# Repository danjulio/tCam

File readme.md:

## ESP32-based Thermal Imaging Cameras
tCam, tCam-Mini, tCam-POE and tCam-Eth are four cameras designed by Dan Julio around the ESP32 and Lepton 3.5.  They provide easy access to radiometric data from the Lepton — per-pixel temperature information that survives into saved files and enables real analysis, not just pretty pictures.

This fork modernizes the **tCam-Mini firmware** into a fully self-contained instrument: the camera serves its own app to any browser, roams between WiFi networks, updates itself over the air, and needs no software installed anywhere.  The original json protocol on port 5001 is untouched, so every existing client — desktop app, Python scripts, mobile apps — keeps working.

### Quick start (this firmware)
1. Flash `tCam-Mini/firmware` (see [BUILDING_WINDOWS.md](tCam-Mini/firmware/BUILDING_WINDOWS.md)) — or upload a built `tCamMini.bin` through the web UI of any camera already running FW 4.0+.
2. Power the camera.  It joins a saved WiFi network, or broadcasts its own `tCam-Mini-XXXX` hotspot.
3. Connect and browse to **http://192.168.58.1/** (hotspot) or **http://tcam-mini.local** (your network).  That's the whole app.

| | |
|---|---|
|  |  |
| *Instrument-dense settings; the ⓘ button reveals help text.* | *Full toolbar and readouts on a phone.* |

More interface detail and screenshots: [WEB_UI.md](tCam-Mini/firmware/WEB_UI.md)

### Find the camera after it moves — tCam Finder

A saved browser shortcut freezes an IP address, but a camera that roams between houses
gets a different one at each location, so the shortcut opens a dead address. **tCam
Finder** fixes that with a page whose own address never changes: it asks the camera —
over Bluetooth LE — where it is *right now*, then opens its interface.

**➡️ [Open tCam Finder](https://mcgeaverbeaver.github.io/tCam/)** — save *this* page to
your home screen instead of the camera's IP.

| | |
|---|---|
|  |  |
| *Find by Bluetooth, plus every camera it has seen before.* | *[▶ Watch the demo](https://youtube.com/shorts/R_bb3d-skMs)* |

Bluetooth is used for **discovery only** — one read of the camera's name, current address
and mode. Video then streams over WiFi at full speed through the normal web interface.
There is no cloud service, no account and no backend: the page is static, all camera
traffic stays on your LAN, and the remembered-camera list lives only in your own browser.
Because the finder's origin is stable, that list survives the address changes that break
a camera-hosted shortcut.

* **Android / Windows / any Chrome or Edge** — *Find my camera*, pick it, done
* **iPhone / iPad / Mac** — no Web Bluetooth; the page offers the `.local` name instead, which mDNS keeps current
* **Camera in hotspot mode** — the page says so and points at `192.168.58.1`

Hosting is just GitHub Pages from [`docs/`](docs/) — fork the repo, enable Pages, and the
finder is yours. Details and the BLE contract: [docs/README.md](docs/README.md).

### What changed vs. the original firmware

| | Original (FW 3.x) | This fork (FW 6.15) |
|---|---|---|
| Viewer | Desktop/mobile app required | Any browser — nothing to install; up to 4 viewers at once |
| Streaming | json over TCP :5001 | Same, **plus** compact binary WebSocket to the browser |
| UI | — | Dark instrument UI: palettes, 640×480 upscale, isotherm, spot/probe, °C/°F |
| Recording | Desktop app | In-browser video + PNG, optional burned-in overlay |
| WiFi | One configured SSID | **Roams**: 5 saved networks, joins strongest in sight |
| Unreachable network | Camera unreachable | Own hotspot within seconds, auto-rejoins when found |
| Setup | App/serial | Captive portal: connect to hotspot, page opens itself |
| Firmware update | Serial / desktop app | Drag a .bin into the browser (safe A/B partitions) |
| Discovery | — | mDNS: `tcam-mini.local` + in-app camera finder |
| Find it after it moves | Re-discover by hand | **tCam Finder** page ([docs/](docs/)): Bluetooth LE asks the camera for its current address and opens it |
| Diagnostics | Serial cable | System log in the browser (Settings → System) |
| Sensor protection | — | Shutter parks over detector 10 s after last viewer leaves (sun protection) |
| Platform | ESP-IDF 4.4.4 (EOL 2024) | ESP-IDF 5.5, current drivers throughout |
| Protocol compat | — | Port 5001 json unchanged; `.tjsn` files identical |

Full engineering history: [tCam-Mini/firmware/readme.md](tCam-Mini/firmware/readme.md) · Web UI details: [WEB_UI.md](tCam-Mini/firmware/WEB_UI.md)

Also fixed along the way: command-parser buffer overruns, interrupt-driven Lepton vsync (was a busy-wait), event-driven response task, a display-string overflow, and a latent I2C port-number bug.  Upstream merge requests welcome — the work splits cleanly into fixes, platform port, and features.

### tCam-Mini
tCam-Mini is a smaller camera designed for streaming and remote access.  It supports a Wifi or hardwired interface.  It can be built using development boards or a tested unit can be purchased from Group Gets [with built in antenna](https://store.groupgets.com/products/tcam-mini-rev4-wireless-streaming-thermal-camera-board) or [with an external antenna](https://store.groupgets.com/products/tcam-mini-rev4-external-antenna-wireless-streaming-thermal-camera-board).

(image courtesy of Group Gets)

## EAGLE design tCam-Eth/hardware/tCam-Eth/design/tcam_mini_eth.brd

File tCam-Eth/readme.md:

## tCam-Eth
tCam-Eth was developed for the [FireTIRS](https://github.com/jthompson2710/FireTIRS) project as a small ethernet connected thermal imaging camera.  It runs on 3.3V and exposes the TX and RX differential pairs from the ethernet PHY chip (it does not contain any magnetics), as well as a 3.3V logic serial interface.  It runs the tCam-Mini firmware, starting with version 3.0, and identifies as a tCam-POE device (configured for network operation).

A baseboard containing a USB UART chip and Magjack RJ45 ethernet connector was also developed and is used for initial programming and test of tCam-Eth boards.

This directory contains the hardware design and documentation for both boards.

1. Eagle V7.7 design files.
2. Gerbers (including paste layer for stencils).
3. Bill-of-Material (BOM).
4. Additional electronics documentation such as printed schematics, reference designator drawings, load list, etc.
5. Supporting mechanical designs for spaces and base mounts.

Please see the tCam-Mini directory for a detailed description of the command interface.

### Dimensions

tCam-Eth is 1.25 x 1.5" (31.75 x 38.10mm).

tCam-Eth Baseboard is 2 x 2.75" (50.8 x 69.85mm).

### Lepton Compatibility
tCam-Eth works with the following Lepton camera modules.

1. Lepton 3.0
2. Lepton 3.1R
3. Lepton 3.5

### Hardware Interfaces

#### tCam-Eth Hardware Interface
Connector CON1 (tCam-Eth PCB bottom) contains the following signals.

| Pin | Description |
| --- | --- |
| 1 | Ground |
| 2 | Ethernet TD+ (PHY output) |
| 3 | Ethernet TD- (PHY output) |
| 4 | Ground |
| 5 | Serial DTRN input (3.3V logic) |
| 6 | Serial RTSN input (3.3V logic) |
| 7 | Ground |
| 8 | +3.3V Power |
| 9 | +3.3V Power |
| 10 | Ground |
| 11 | Serial RX input (3.3V logic) |
| 12 | Serial TX output (3.3V logic) |
| 13 | Ground |
| 14 | Ethernet RX+ (PHY input) |
| 15 | Ethernet RX- (PHY input) |
| 16 | Ground |

The external 3.3V power supply must be regulated to +/- 5% and capable of supplying 500 mA (typical current consumption is < 200 mA).

#### tCam-Eth Baseboard Hardware Interfaces
Connector J1 is a USB-C connector used to provide power and serial communications.

Connector J2 is a RJ45 connector used to provide 10/100M bps ethernet communications.

### Operation
tCam-Eth is a command-based device.  It is designed for software running on another device to control it and receive responses and image data from it.  The command interface is described in the tCam-Mini firmware directory.

#### Ethernet Port
The ethernet port support an IEEE 803.2 10/100 Mbps ethernet interface.  tCam-Eth provides the direct TX and RX differential pairs from the on-board PHY chip.  It may be used in a direct connect fashion (as is done on the FireTIRS board) or with a traditional set of magnetics connected to an isolated RJ45 jack (as is done on the tCam-Eth Baseboard).

tCam-Eth can obtain a DHCP served address from a router on the network or may be configured with a static IP address.

#### Serial Port
tCam-Eth provides a 3.3V logic-level serial interface along with RTSN and DTRN flow-control inputs.  These are used to load firmware into the on-board ESP32 micro-controller (for example using the tCam-Eth Baseboard).  They may also be used to monitor the diagnostic serial output while the firmware is running.

#### Status Indicators
A dual-color (red/green) LED is used to communicate status (reference designator LED3).  Combinations of color and blinking patterns communicate various information.

| Status Indicator | Meaning |
| --- | --- |
| Off or Dim | Firmware did not start |
| Solid Red | Firmware is running: initializing and configuring the Lepton and Ethernet interface |
| Blinking Yellow | No ethernet network detected |
| Solid Yellow | Ethernet is connected and the camera has an IP address |
| Solid Green | Ethernet is connected and external software has connected via the socket interface |
| Fast Blink Yellow | Network Reset in progress |
| Alternating Red/Green | Over-the-air (network) FW update has been requested.  Press the button to initiate the update |
| Blinking Green | FW update in process (blinking my occur at irregular intervals as the Flash memory is written) |
| Series of Red Blinks | A fault has been detected.  The number of blinks indicate the fault type (see table below) |

| Fault Blinks | Meaning |
| --- | --- |
| 1 blink | ESP32 I2C or SPI peripheral initialization failed |
| 2 blinks | ESP32 Non-volatile storage or Network initialization failed |
| 3 blinks | ESP32 static memory buffer allocation failed (potential PSRAM issue) |
| 4 blinks | Lepton CCI communication failed (I2C interface) |
| 5 blinks | Lepton VoSPI communication failed (SPI interface) |
| 6 blinks | Internal network error occurred |
| 7 blinks | Lepton VoSPI synchronization cannot be achieved |
| 8 blinks | Over-the-air FW Update failed |

Additional start-up and fault information is available from the Serial interface.

A single-color yellow LED is used to communicate network Link/Activity (reference designator LED1).

A single-color green LED is used to communicate network 100 Mbit operation (reference designator LED2).

#### Network Reset Button
Pressing and holding the Network Reset Button for more than five seconds resets the network interface back to the default mode (requesting a DHCP served address).

Pressing the button quickly when an OTA FW update has been requested (LED alternating red/green) by the Desktop application initiates the update process.

#### mDNS Discovery
The cameras advertise themselves on the local network using mDNS (Bonjour) to make discovering their IPV4 addresses easier.

* Service Type: "\_tcam-socket._tcp."
* Host/Instance Name: Camera Name (e.g. "tCam-Mini-821F")
* TXT Records:
	1. "model": Camera model (always "tCam-POE")
	2. "interface": Communication interface (always "Ethernet")
	3. "version": Firmware version (e.g. "3.2")

### Mounting Hardware
Three supporting hardware pieces, designed using OpenSCAD, are designed to be 3D printed.  Both the OpenSCAD source and compiled STL files are included.

### Application spacer
The Application spacer is designed to mount tCam-Eth board to the application PCB via 4 M2x8mm screws, nuts and washers.  The cutout region aligns with the connector end of tCam-Eth.

### Baseboard spacer
The Baseboard spacer is designed to be mounted (carefully aligned) on the Baseboard using double-sticky tape or screws from the bottom.  It holds the tCam-Eth board in the correct position but makes it easy to insert and remove.

### Baseboard mount
The Baseboard mount is designed to hold the tCam-Eth Baseboard.  The Baseboard is screwed to the mount using #4, M3 or similar pointed screws.

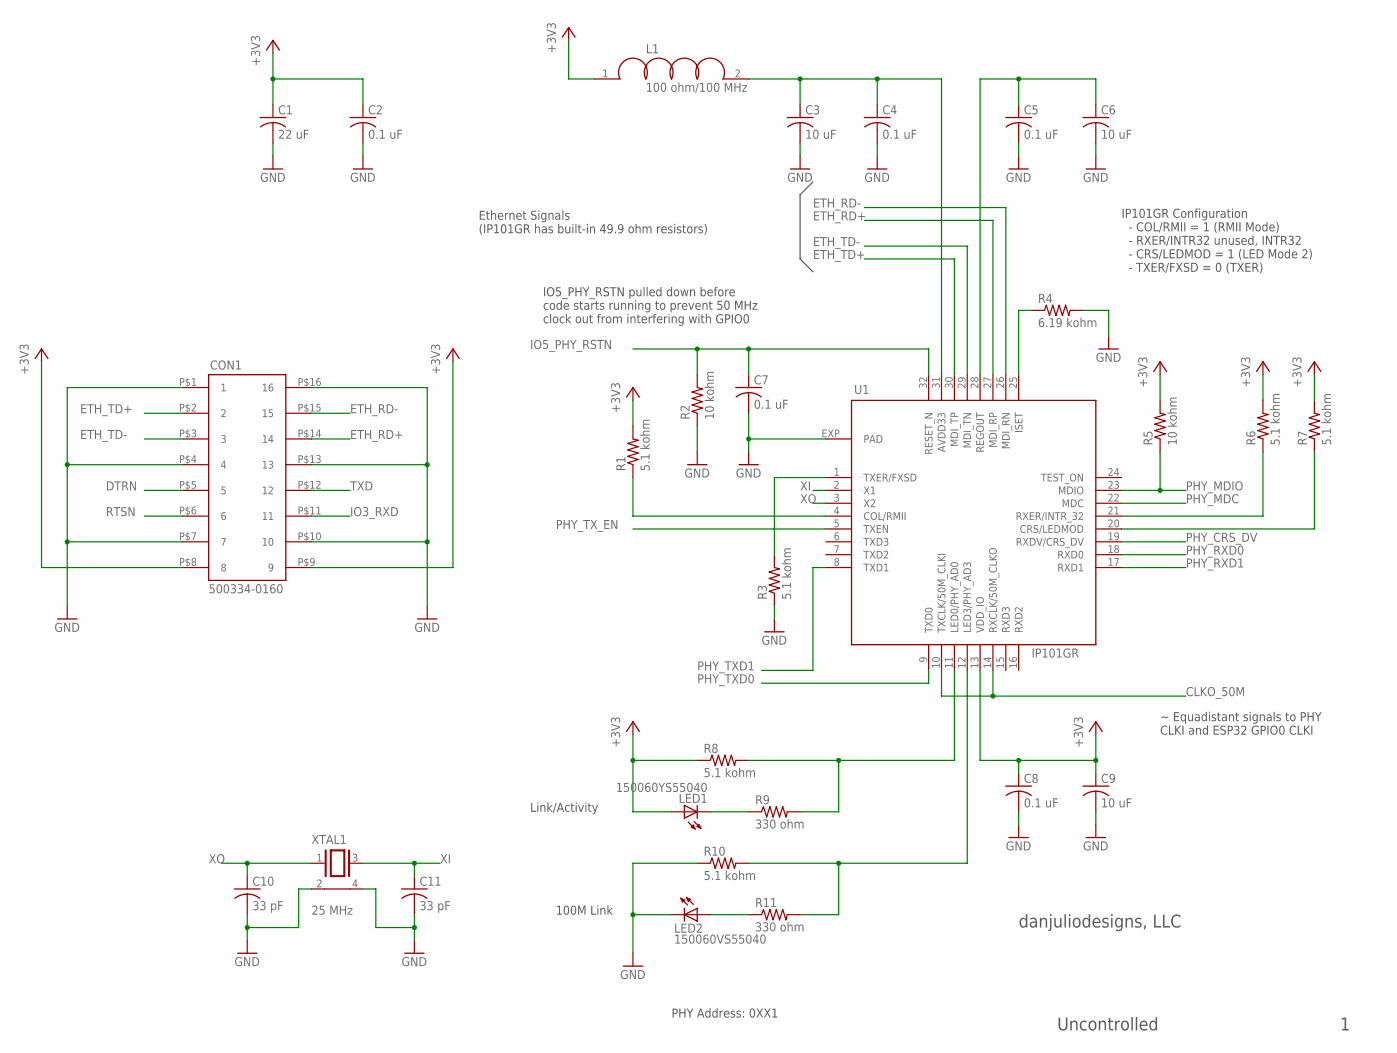
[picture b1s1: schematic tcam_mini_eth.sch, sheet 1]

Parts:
C1: 22 uF; C0603
C2, C4, C5, C7, C8: 0.1 uF; C0402
C3, C6, C9: 10 uF; C0603
C10, C11: 33 pF; C0402
CON1: 500334-0160; MOLEX_500334_0160
L1: 100 ohm/100 MHz; L0603
LED1: 150060YS55040; CHIPLED_0603
LED2: 150060VS55040; CHIPLED_0603
R1, R3, R6, R7, R8, R10: 5.1 kohm; R0402
R2, R5: 10 kohm; R0402
R4: 6.19 kohm; R0402
R9, R11: 330 ohm; R0402
U1: IP101GR; QFN32_4X4
XTAL1: 25 MHz; CRYSTAL-3225

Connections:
+3V3: C1.1, C2.1, C8.1, C9.1, CON1.P$8 (8), CON1.P$9 (9), L1.1, LED1.A, R1.2, R5.2, R6.2, R7.2, R8.1, U1.13 (VDD_IO); also elsewhere on the board
CLKO_50M: U1.10 (TXCLK/50M_CLKI), U1.14 (RXCLK/50M_CLKO); also elsewhere on the board
DTRN: CON1.P$5 (5); also elsewhere on the board
ETH_RD+: CON1.P$14 (14), U1.27 (MDI_RP)
ETH_RD-: CON1.P$15 (15), U1.26 (MDI_RN)
ETH_TD+: CON1.P$2 (2), U1.30 (MDI_TP)
ETH_TD-: CON1.P$3 (3), U1.29 (MDI_TN)
GND: C1.2, C2.2, C3.2, C4.2, C5.2, C6.2, C7.2, C8.2, C9.2, C10.2, C11.2, CON1.P$1 (1), CON1.P$4 (4), CON1.P$7 (7), CON1.P$10 (10), CON1.P$13 (13), CON1.P$16 (16), LED2.C, R2.1, R3.1, R4.2, R10.1, U1.EXP (PAD), XTAL1.2, XTAL1.4; also elsewhere on the board
IO3_RXD: CON1.P$11 (11); also elsewhere on the board
IO5_PHY_RSTN: C7.1, R2.2, U1.32 (RESET_N); also elsewhere on the board
unnamed: C3.1, C4.1, L1.2, U1.31 (AVDD33)
unnamed: R4.1, U1.25 (ISET)
unnamed: R6.1, U1.21 (RXER/INTR_32)
unnamed: R1.1, U1.4 (COL/RMII)
unnamed: R3.2, U1.1 (TXER/FXSD)
unnamed: R7.1, U1.20 (CRS/LEDMOD)
unnamed: R8.2, R9.2, U1.11 (LED0/PHY_AD0)
unnamed: R10.2, R11.2, U1.12 (LED3/PHY_AD3)
unnamed: LED2.A, R11.1
unnamed: LED1.C, R9.1
PHY_CRS_DV: U1.19 (RXDV/CRS_DV); also elsewhere on the board
PHY_MDC: U1.22 (MDC); also elsewhere on the board
PHY_MDIO: R5.1, U1.23 (MDIO); also elsewhere on the board
PHY_RXD0: U1.18 (RXD0); also elsewhere on the board
PHY_RXD1: U1.17 (RXD1); also elsewhere on the board
PHY_TXD0: U1.9 (TXD0); also elsewhere on the board
PHY_TXD1: U1.8 (TXD1); also elsewhere on the board
PHY_TX_EN: U1.5 (TXEN); also elsewhere on the board
REGOUT: C5.1, C6.1, U1.28 (REGOUT)
RTSN: CON1.P$6 (6); also elsewhere on the board
TXD: CON1.P$12 (12); also elsewhere on the board
XI: C11.1, U1.2 (X1), XTAL1.3
XO: C10.1, U1.3 (X2), XTAL1.1

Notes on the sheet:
IO5_PHY_RSTN pulled down before code starts running to prevent 50 MHz clock out from interfering with GPIO0
Ethernet Signals (IP101GR has built-in 49.9 ohm resistors)
~ Equadistant signals to PHY CLKI and ESP32 GPIO0 CLKI
IP101GR Configuration - COL/RMII = 1 (RMII Mode) - RXER/INTR32 unused, INTR32 - CRS/LEDMOD = 1 (LED Mode 2) - TXER/FXSD = 0 (TXER)
PHY Address: 0XX1
100M Link
Link/Activity
danjuliodesigns, LLC
Uncontrolled

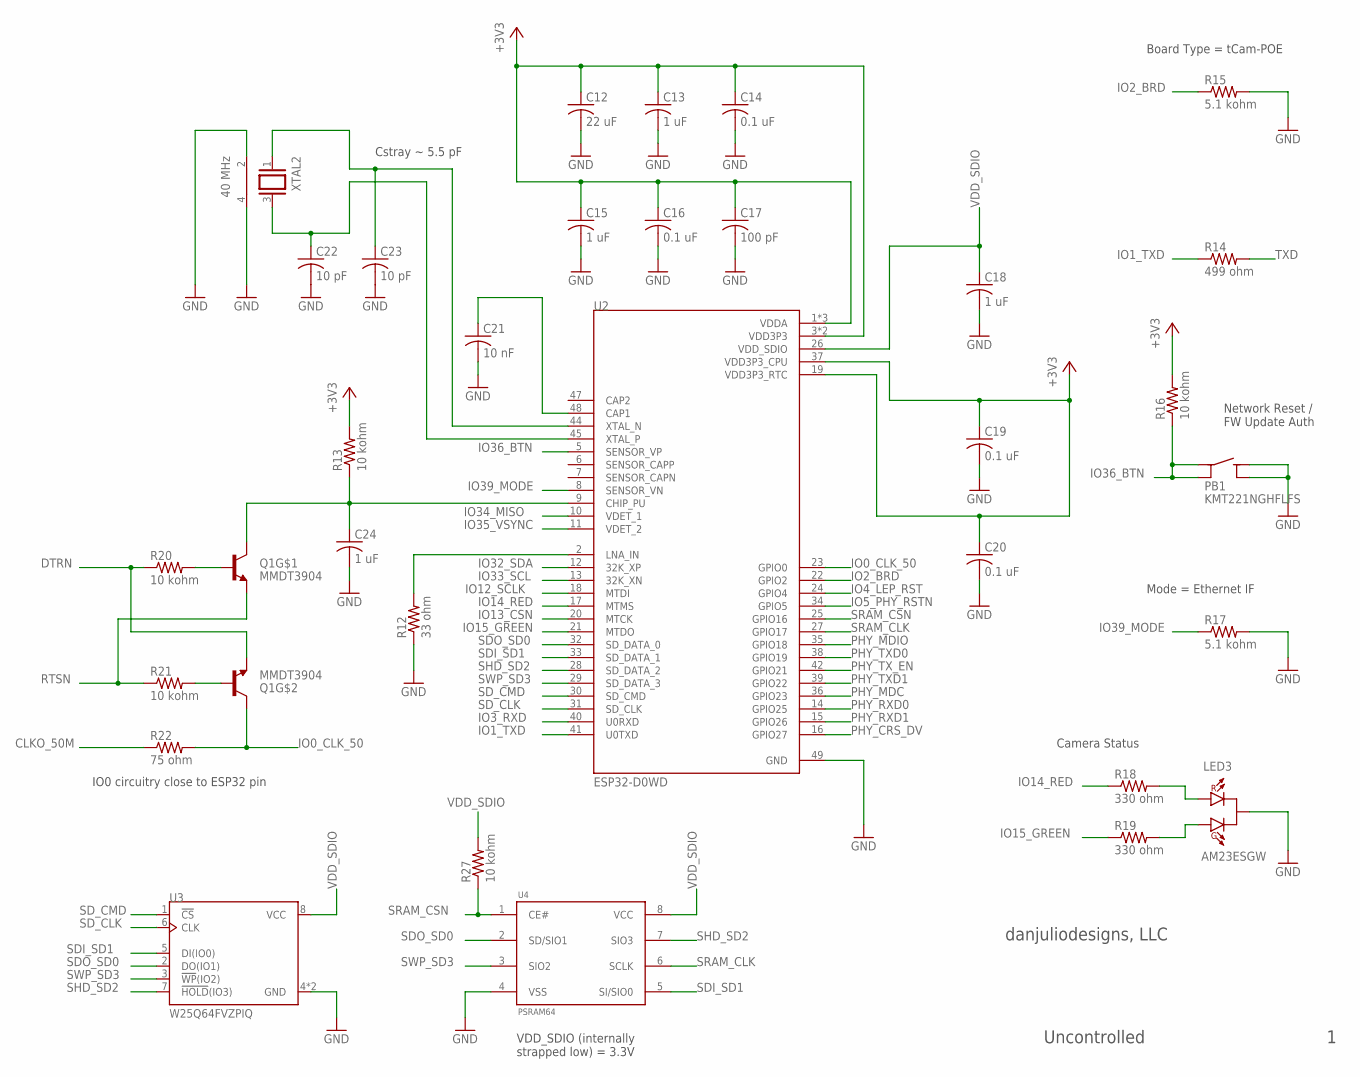
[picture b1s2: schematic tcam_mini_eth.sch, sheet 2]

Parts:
C12: 22 uF; C0603
C13, C15, C18, C24: 1 uF; C0402
C14, C16, C19, C20: 0.1 uF; C0402
C17: 100 pF; C0402
C21: 10 nF; C0402
C22, C23: 10 pF; C0402
LED3: AM23ESGW; SOT23-3
PB1: KMT221NGHFLFS; CK_KMT2
Q1: MMDT3904; SOT363
R12: 33 ohm; R0603
R13, R16, R20, R21, R27: 10 kohm; R0402
R14: 499 ohm; R0402
R15, R17: 5.1 kohm; R0402
R18, R19: 330 ohm; R0402
R22: 75 ohm; R0402
U2: ESP32-D0WD; QFN35P500X500X90-49N
U3: W25Q64FVZPIQ; SON127P600X500X80-9N
U4: PSRAM64; SO8
XTAL2: 40 MHz; CRYSTAL-3225

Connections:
+3V3: C12.1, C13.1, C14.1, C15.1, C16.1, C17.1, C19.1, C20.1, R13.2, R16.2, U2.1 (VDDA), U2.3 (VDD3P3), U2.4 (VDD3P3), U2.19 (VDD3P3_RTC), U2.37 (VDD3P3_CPU), U2.43 (VDDA), U2.46 (VDDA); also elsewhere on the board
CLKO_50M: R22.1; also elsewhere on the board
DTRN: Q1.1 (E), R20.1; also elsewhere on the board
GND: C12.2, C13.2, C14.2, C15.2, C16.2, C17.2, C18.2, C19.2, C20.2, C21.2, C22.2, C23.2, C24.2, LED3.3 (C), PB1.3, PB1.4, R12.1, R15.2, R17.2, U2.49 (GND), U3.4 (GND), U3.9 (GND), U4.4 (VSS), XTAL2.2, XTAL2.4; also elsewhere on the board
IO0_CLK_50: Q1.6 (C), R22.2, U2.23 (GPIO0)
IO1_TXD: R14.1, U2.41 (U0TXD)
IO2_BRD: R15.1, U2.22 (GPIO2)
IO3_RXD: U2.40 (U0RXD); also elsewhere on the board
IO4_LEP_RST: U2.24 (GPIO4); also elsewhere on the board
IO5_PHY_RSTN: U2.34 (GPIO5); also elsewhere on the board
IO12_SCLK: U2.18 (MTDI); also elsewhere on the board
IO13_CSN: U2.20 (MTCK); also elsewhere on the board
IO14_RED: R18.1, U2.17 (MTMS)
IO15_GREEN: R19.1, U2.21 (MTDO)
IO32_SDA: U2.12 (32K_XP); also elsewhere on the board
IO33_SCL: U2.13 (32K_XN); also elsewhere on the board
IO34_MISO: U2.10 (VDET_1); also elsewhere on the board
IO35_VSYNC: U2.11 (VDET_2); also elsewhere on the board
IO36_BTN: PB1.1, PB1.2, R16.1, U2.5 (SENSOR_VP)
IO39_MODE: R17.1, U2.8 (SENSOR_VN)
unnamed: C23.1, U2.44 (XTAL_N), XTAL2.1
unnamed: C22.1, U2.45 (XTAL_P), XTAL2.3
unnamed: LED3.1 (RA), R18.2
unnamed: C24.1, Q1.3 (C), R13.1, U2.9 (CHIP_PU)
unnamed: R12.2, U2.2 (LNA_IN)
unnamed: C21.1, U2.48 (CAP1)
unnamed: LED3.2 (GA), R19.2
unnamed: Q1.2 (B), R21.2
unnamed: Q1.5 (B), R20.2
PHY_CRS_DV: U2.16 (GPIO27); also elsewhere on the board
PHY_MDC: U2.36 (GPIO23); also elsewhere on the board
PHY_MDIO: U2.35 (GPIO18); also elsewhere on the board
PHY_RXD0: U2.14 (GPIO25); also elsewhere on the board
PHY_RXD1: U2.15 (GPIO26); also elsewhere on the board
PHY_TXD0: U2.38 (GPIO19); also elsewhere on the board
PHY_TXD1: U2.39 (GPIO22); also elsewhere on the board
PHY_TX_EN: U2.42 (GPIO21); also elsewhere on the board
RTSN: Q1.4 (E), R21.1; also elsewhere on the board
SDI_SD1: U2.33 (SD_DATA_1), U3.5 (DI(IO0)), U4.5 (SI/SIO0)
SDO_SD0: U2.32 (SD_DATA_0), U3.2 (DO(IO1)), U4.2 (SD/SIO1)
SD_CLK: U2.31 (SD_CLK), U3.6 (CLK)
SD_CMD: U2.30 (SD_CMD), U3.1 (!CS)
SHD_SD2: U2.28 (SD_DATA_2), U3.7 (!HOLD!(IO3)), U4.7 (SIO3)
SRAM_CLK: U2.27 (GPIO17), U4.6 (SCLK)
SRAM_CSN: R27.1, U2.25 (GPIO16), U4.1 (CE#)
SWP_SD3: U2.29 (SD_DATA_3), U3.3 (!WP!(IO2)), U4.3 (SIO2)
TXD: R14.2; also elsewhere on the board
VDD_SDIO: C18.1, R27.2, U2.26 (VDD_SDIO), U3.8 (VCC), U4.8 (VCC)

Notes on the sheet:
Board Type = tCam-POE
VDD_SDIO (internally strapped low) = 3.3V
Network Reset / FW Update Auth
Mode = Ethernet IF
Camera Status
IO0 circuitry close to ESP32 pin
Cstray ~ 5.5 pF
danjuliodesigns, LLC
Uncontrolled

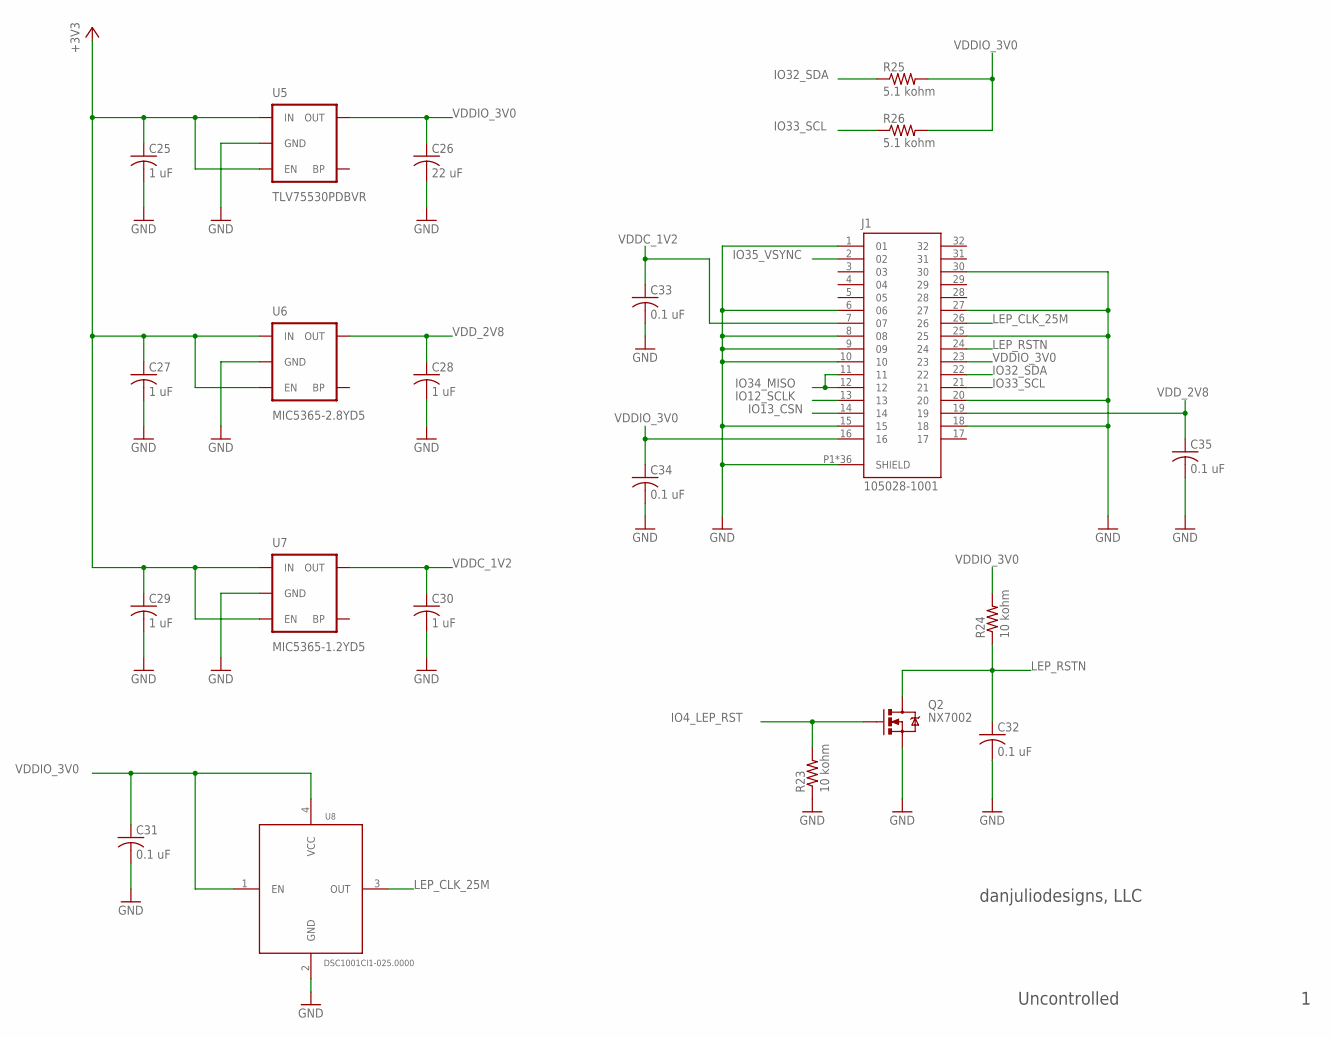
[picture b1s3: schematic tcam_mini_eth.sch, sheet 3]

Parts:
C25, C27, C28, C29, C30: 1 uF; C0402
C26: 22 uF; C0603
C31, C32, C33, C34, C35: 0.1 uF; C0402
J1: 105028-1001; MOLEX_105028-1001
Q2: NX7002; SOT23-3
R23, R24: 10 kohm; R0402
R25, R26: 5.1 kohm; R0402
U5: TLV75530PDBVR; SOT23-5
U6: MIC5365-2.8YD5; SOT23-5
U7: MIC5365-1.2YD5; SOT23-5
U8: DSC1001CI1-025.0000; CRYSTAL-3225

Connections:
+3V3: C25.1, C27.1, C29.1, U5.1 (IN), U5.3 (EN), U6.1 (IN), U6.3 (EN), U7.1 (IN), U7.3 (EN); also elsewhere on the board
GND: C25.2, C26.2, C27.2, C28.2, C29.2, C30.2, C31.2, C32.2, C33.2, C34.2, C35.2, J1.1, J1.6, J1.8, J1.9, J1.10, J1.15, J1.18, J1.20, J1.25, J1.27, J1.30, J1.P1 (SHIELD), J1.P2 (SHIELD), J1.P3 (SHIELD), J1.P4 (SHIELD), J1.P5 (SHIELD), J1.P6 (SHIELD), J1.P7 (SHIELD), J1.P8 (SHIELD), J1.P9 (SHIELD), J1.P10 (SHIELD), J1.P11 (SHIELD), J1.P12 (SHIELD), J1.P13 (SHIELD), J1.P14 (SHIELD), J1.P15 (SHIELD), J1.P16 (SHIELD), J1.P17 (SHIELD), J1.P18 (SHIELD), J1.P19 (SHIELD), J1.P20 (SHIELD), J1.P21 (SHIELD), J1.P22 (SHIELD), J1.P23 (SHIELD), J1.P24 (SHIELD), J1.P25 (SHIELD), J1.P26 (SHIELD), J1.P27 (SHIELD), J1.P28 (SHIELD), J1.P29 (SHIELD), J1.P30 (SHIELD), J1.P31 (SHIELD), J1.P32 (SHIELD), J1.P33 (SHIELD), J1.P34 (SHIELD), J1.P35 (SHIELD), J1.P36 (SHIELD), Q2.2 (S), R23.1, U5.2 (GND), U6.2 (GND), U7.2 (GND), U8.2 (GND); also elsewhere on the board
IO4_LEP_RST: Q2.1 (G), R23.2; also elsewhere on the board
IO12_SCLK: J1.13; also elsewhere on the board
IO13_CSN: J1.14; also elsewhere on the board
IO32_SDA: J1.22, R25.1; also elsewhere on the board
IO33_SCL: J1.21, R26.1; also elsewhere on the board
IO34_MISO: J1.11, J1.12; also elsewhere on the board
IO35_VSYNC: J1.2; also elsewhere on the board
LEP_CLK_25M: J1.26, U8.3 (OUT)
LEP_RSTN: C32.1, J1.24, Q2.3 (D), R24.1
VDDC_1V2: C30.1, C33.1, J1.7, U7.5 (OUT)
VDDIO_3V0: C26.1, C31.1, C34.1, J1.16, J1.23, R24.2, R25.2, R26.2, U5.5 (OUT), U8.1 (EN), U8.4 (VCC)
VDD_2V8: C28.1, C35.1, J1.19, U6.5 (OUT)

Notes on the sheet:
danjuliodesigns, LLC
Uncontrolled

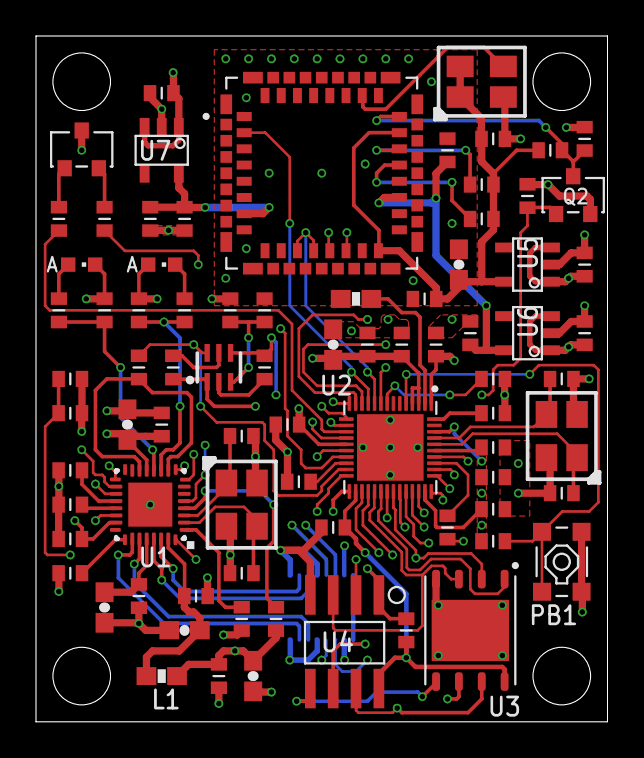
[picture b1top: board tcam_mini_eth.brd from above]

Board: 4 copper layers, 31.8 x 38.1 mm, 81 parts (1 on the bottom side), 70 nets.

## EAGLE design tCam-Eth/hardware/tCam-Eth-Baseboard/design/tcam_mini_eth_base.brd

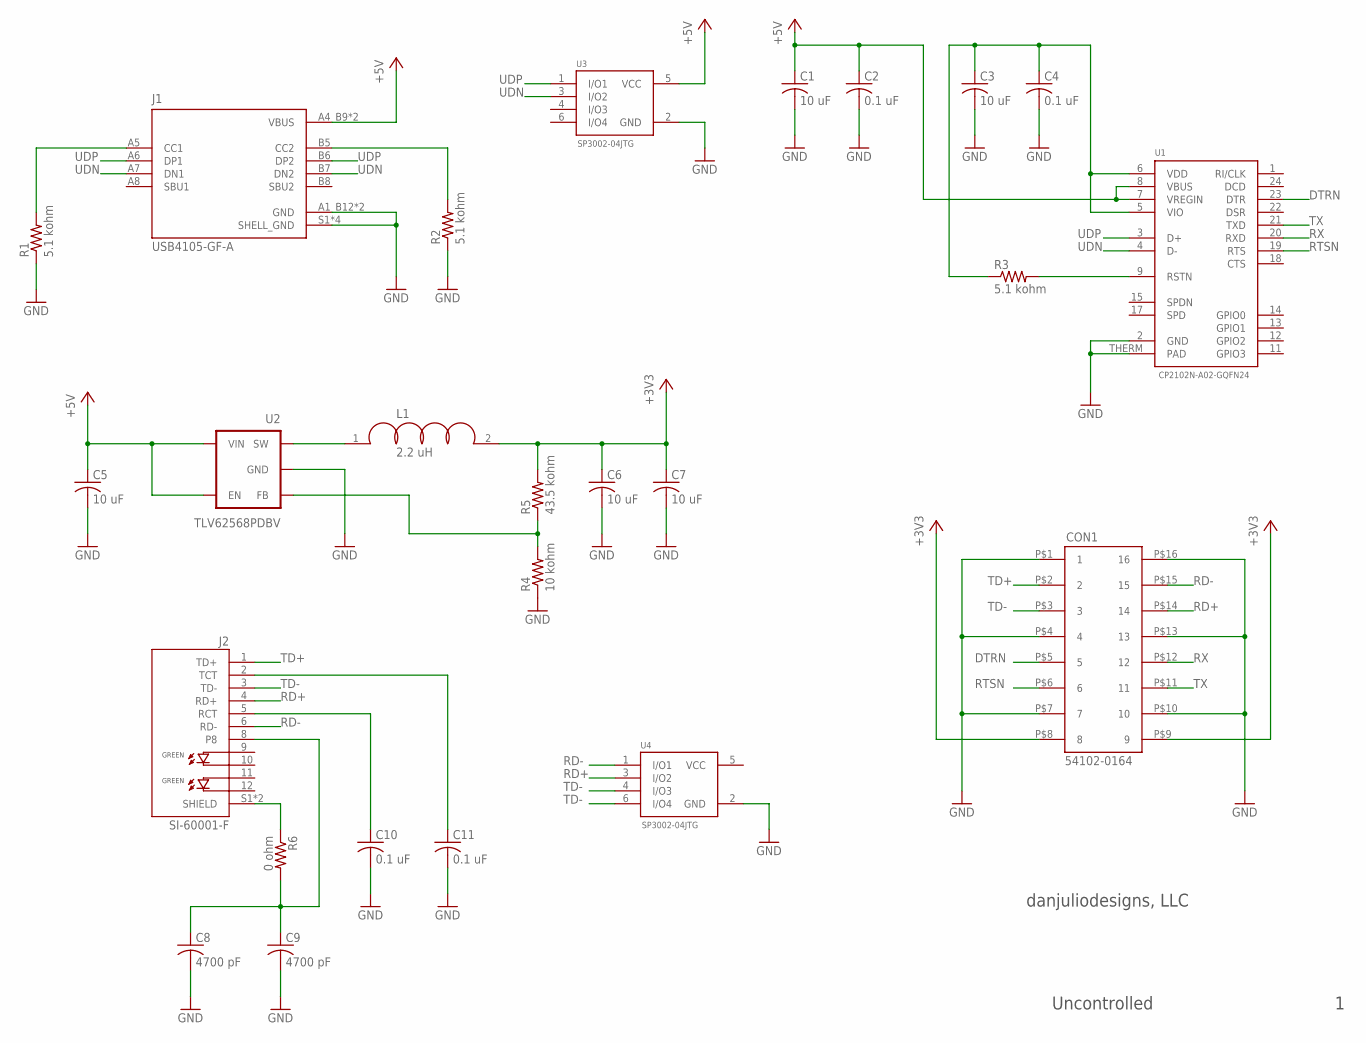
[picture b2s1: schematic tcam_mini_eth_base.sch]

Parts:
C1, C3, C5, C6, C7: 10 uF; C0603
C2, C4, C10, C11: 0.1 uF; C0603
C8, C9: 4700 pF; C1210
CON1: 54102-0164; MOLEX_54102_0164
J1: USB4105-GF-A; GCT_USB4105-GF-A
J2: SI-60001-F; BEL_SI-60001-F
L1: 2.2 uH; L1008
R1, R2, R3: 5.1 kohm; R0603
R4: 10 kohm; R0603
R5: 43.5 kohm; R0603
R6: 0 ohm; R0805
U1: CP2102N-A02-GQFN24; QFN24
U2: TLV62568PDBV; SOT23-5
U3, U4: SP3002-04JTG; SOT65P220X95-6N

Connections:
+3V3: C6.1, C7.1, CON1.P$8 (8), CON1.P$9 (9), L1.2, R5.2
+5V: C1.1, C2.1, C5.1, J1.A4_B9 (VBUS), J1.B4_A9 (VBUS), U1.7 (VREGIN), U1.8 (VBUS), U2.1 (EN), U2.4 (VIN), U3.5 (VCC)
DTRN: CON1.P$5 (5), U1.23 (DTR)
GND: C1.2, C2.2, C3.2, C4.2, C5.2, C6.2, C7.2, C8.2, C9.2, C10.2, C11.2, CON1.P$1 (1), CON1.P$4 (4), CON1.P$7 (7), CON1.P$10 (10), CON1.P$13 (13), CON1.P$16 (16), J1.A1_B12 (GND), J1.B1_A12 (GND), J1.S1 (SHELL_GND), J1.S2 (SHELL_GND), J1.S3 (SHELL_GND), J1.S4 (SHELL_GND), R1.1, R2.1, R4.1, U1.2 (GND), U1.THERM (PAD), U2.2 (GND), U3.2 (GND), U4.2 (GND)
unnamed: J1.A5 (CC1), R1.2
unnamed: J1.B5 (CC2), R2.2
unnamed: L1.1, U2.3 (SW)
unnamed: R4.2, R5.1, U2.5 (FB)
unnamed: R3.2, U1.9 (RSTN)
unnamed: C10.1, J2.5 (RCT)
unnamed: C11.1, J2.2 (TCT)
unnamed: J2.S1 (SHIELD), J2.S2 (SHIELD), R6.1
unnamed: C8.1, C9.1, J2.8, R6.2
RD+: CON1.P$14 (14), J2.4 (RD+), U4.3 (I/O2)
RD-: CON1.P$15 (15), J2.6 (RD-), U4.1 (I/O1)
RTSN: CON1.P$6 (6), U1.19 (RTS)
RX: CON1.P$12 (12), U1.20 (RXD)
TD+: CON1.P$2 (2), J2.1 (TD+), U4.6 (I/O4)
TD-: CON1.P$3 (3), J2.3 (TD-), U4.4 (I/O3)
TX: CON1.P$11 (11), U1.21 (TXD)
UDN: J1.A7 (DN1), J1.B7 (DN2), U1.4 (D-), U3.3 (I/O2)
UDP: J1.A6 (DP1), J1.B6 (DP2), U1.3 (D+), U3.1 (I/O1)
VCC: U4.5 (VCC)
VDD: C3.1, C4.1, R3.1, U1.5 (VIO), U1.6 (VDD)

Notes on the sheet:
danjuliodesigns, LLC
Uncontrolled

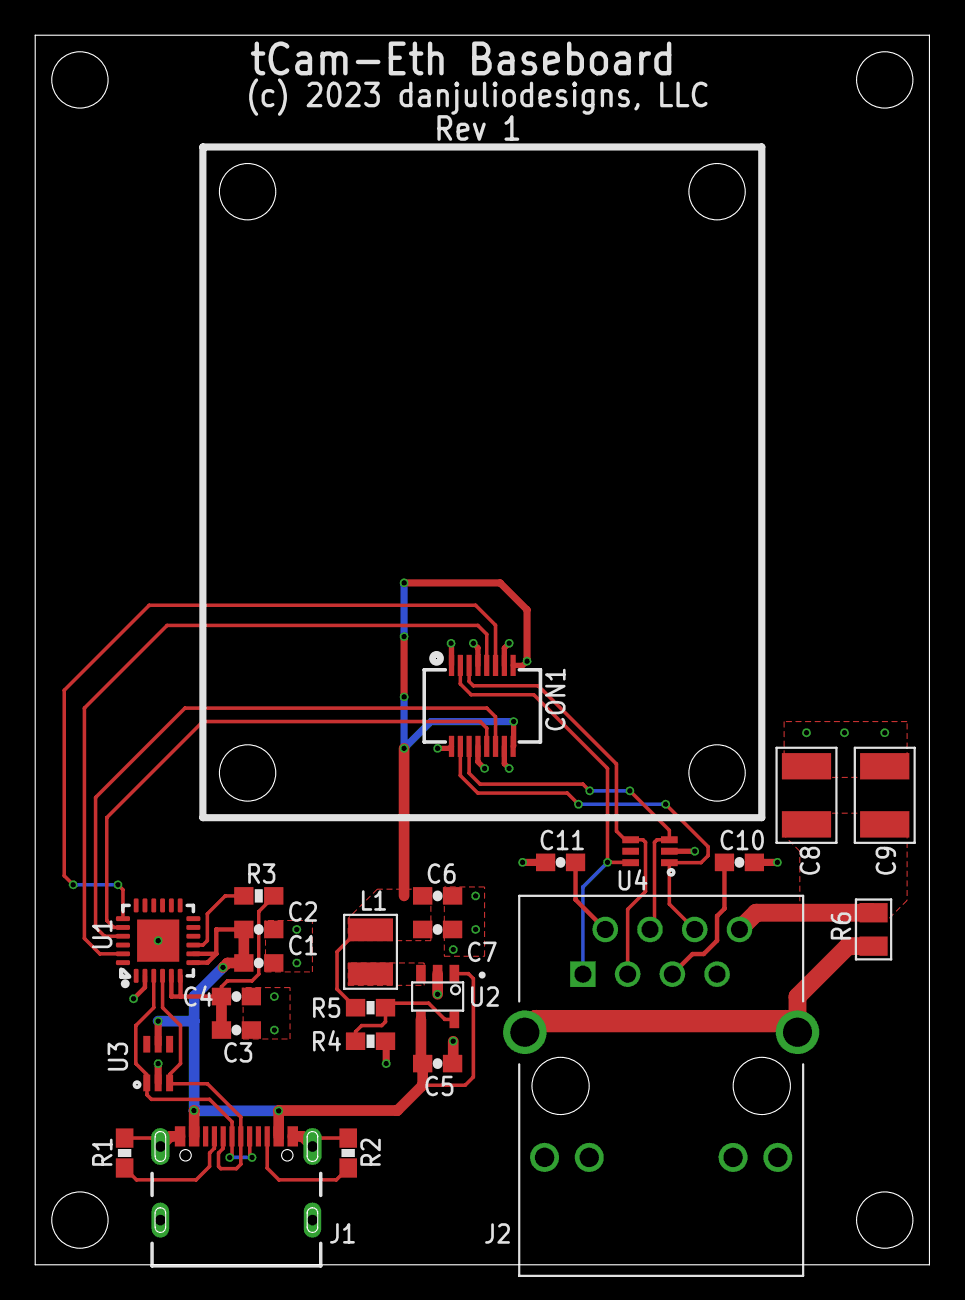
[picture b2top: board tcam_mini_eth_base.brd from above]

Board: 2 copper layers, 50.8 x 69.8 mm, 25 parts (0 on the bottom side), 23 nets.

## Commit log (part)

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2022-11-16 Fixed picture link
2022-12-04 Added missing command descriptions
2023-01-22 Added tCam-POE
2023-01-24 Updated picture
2023-01-30 Added info about tCam Family Serial Updater
2023-02-10 Updated battery info
2023-03-03 Added link to GG Store tCam page
2023-03-07 Added note about protecting Lepton when soldering to tCam-Mini
2023-03-18 * Added Dockerfile for ability to deploy the web application through Docker. * Added instructions on how to use said Dockerfile to build and deploy the server.
2023-03-18 * renamed container name to `tcam-docker` for consistency
2023-03-18 * added missing period (dot) in docker building instructions
2023-03-22 * minor typo fix with chmodding
2023-03-22 accidentally pushed my config; this is not needed
2023-03-24 * Added comments in Dockerfile. Should be more helpful for beginners. * Optimized Docker image size by ~30MB by removing unnecessary packages.
2023-04-06 Added link for Android App
2023-06-19 Added note that Wifi operates in 2.4 GHz band
2023-07-10 Added link to zharijs' enclosures
2023-07-23 Typo
2023-08-17 Added link to CP210X drivers for tCam Family Serial Updater
2023-08-22 Officially support Lepton 3.1R
    Correctly identify Lepton 3.1R production model. tCam-Mini firmware environment moved to IDF 4.4.4. Add 3.1 identification field to camera status Lepton Type.
2023-09-13 Desktop App version 3.2.0
2023-09-13 tCam Firmware version 1.0
2024-07-04 Added tCam-Eth

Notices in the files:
tCam-Eth/hardware/tCam-Eth-Baseboard/design/tcam_mini_eth_base.brd:
(c) 2023 danjuliodesigns, LLC
parts and their libraries:
SparkFun-DiscreteSemi: Licensing: Creative Commons ShareAlike 4.0 International - https://creativecommons.org/licenses/by-sa/4.0
